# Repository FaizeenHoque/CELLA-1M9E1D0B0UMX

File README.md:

# CELLA 1M9E1D0B0UCX

> A minimal 9-key macropad with rotary encoder. Custom PCB, XIAO RP2040, KMK firmware.

---

## Specs

| | |
|---|---|
| MCU | Seeed XIAO RP2040 |
| Switches | 9× MX-compatible (3×3 matrix) |
| Encoder | 1× rotary with push switch |
| Display | None |
| Bluetooth | No |
| Connector | USB-C |
| Firmware | KMK on CircuitPython |
| PCB | Custom, KiCad |

---

## Naming Convention

`CELLA [V][T][K]E[E#]D[D#]B[B#][CON][CASE]`

| Code | Meaning | Values |
|------|---------|--------|
| `V` | Version | `1`, `2`, `3`... |
| `T` | Type | `M` Macro · `N` Numpad · `D` Dial |
| `K` | Key count | `9`, `12`, `16`... |
| `E#` | Encoder | `E1` yes · `E0` no |
| `D#` | Display | `D1` yes · `D0` no |
| `B#` | Bluetooth | `B1` yes · `B0` no |
| `CON` | Connector | `UC` USB-C · `UM` Micro-B |
| `CASE` | Case | `C` clear · `B` black · `W` white · `X` no case |

**Example:** `CELLA 1M9E1D0B0UCX` — Version 1, Macro, 9 keys, 1 encoder, no display, no bluetooth, USB-C, no case.

---

## Renders

---

## License

© 2025 Faizeen Hoque

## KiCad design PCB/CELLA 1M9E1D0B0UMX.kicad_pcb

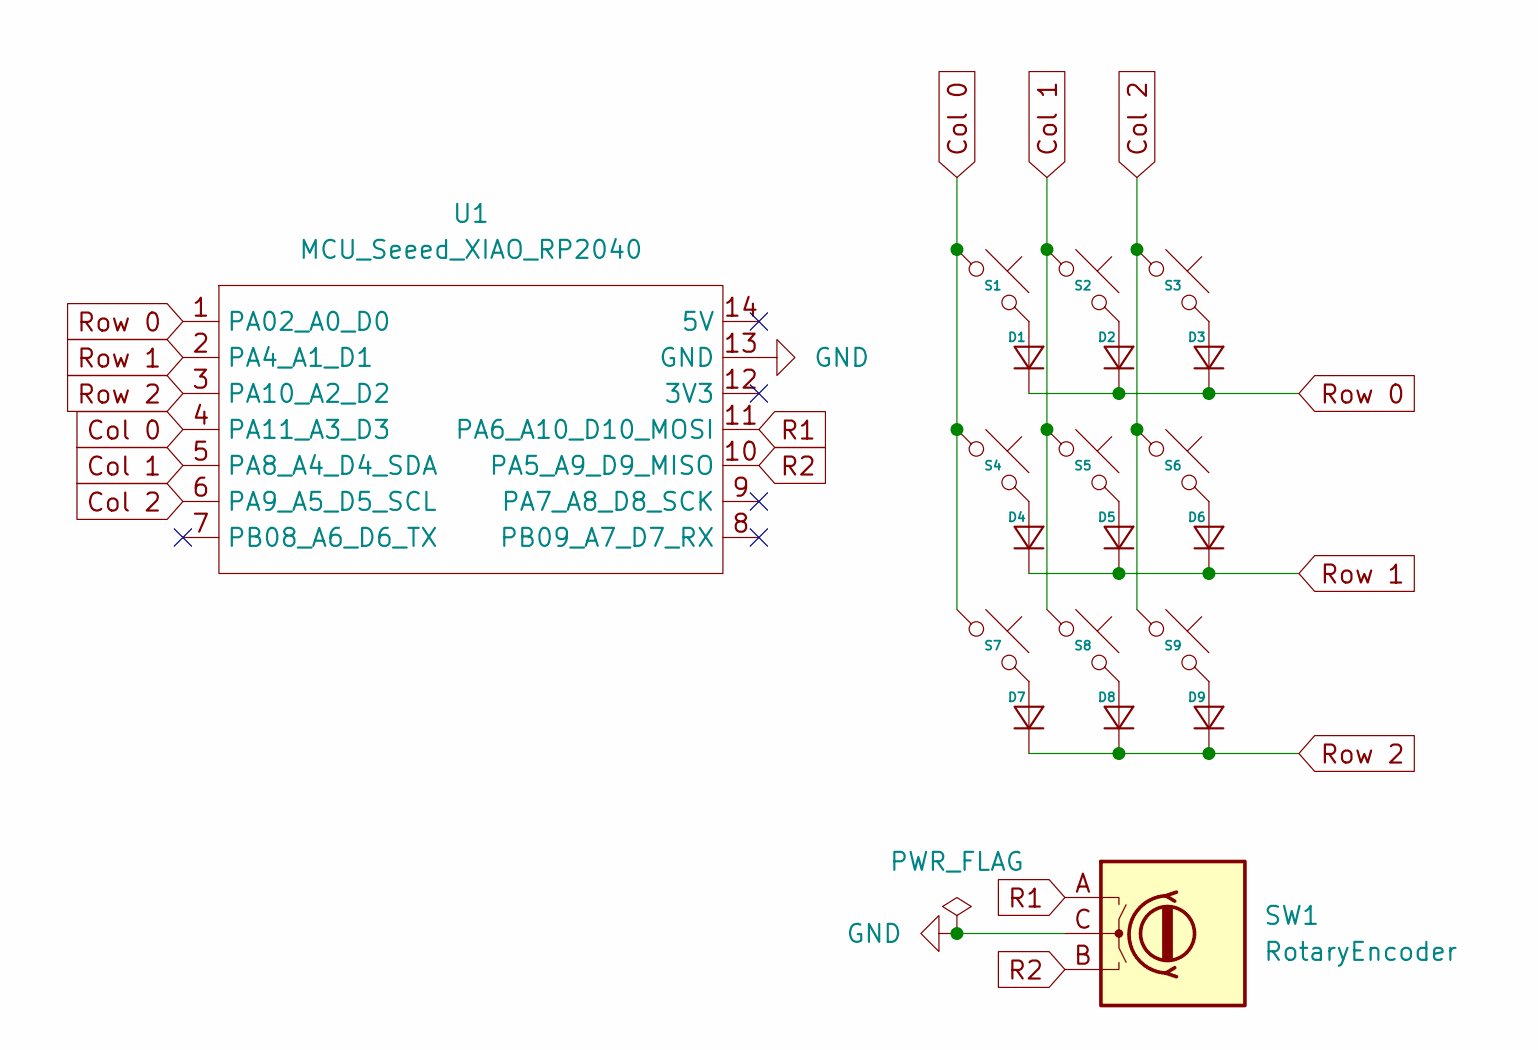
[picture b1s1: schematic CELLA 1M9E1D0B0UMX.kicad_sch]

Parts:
D1, D2, D3, D4, D5, D6, D7, D8, D9: Diode_DO-35
S1, S2, S3, S4, S5, S6, S7, S8, S9: MX_PCB_1.00u
SW1: RotaryEncoder; Encoder_EC11_MX
U1: MCU_Seeed_XIAO_RP2040; Seeed_XIAO_RP2040

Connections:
Col 0: S1.1, S4.1, S7.1, U1.4 (PA11_A3_D3)
Col 1: S2.1, S5.1, S8.1, U1.5 (PA8_A4_D4_SDA)
Col 2: S3.1, S6.1, S9.1, U1.6 (PA9_A5_D5_SCL)
GND: SW1.C, U1.13 (GND)
unnamed: D1.2 (A), S1.2
unnamed: D2.2 (A), S2.2
unnamed: D3.2 (A), S3.2
unnamed: D4.2 (A), S4.2
unnamed: D5.2 (A), S5.2
unnamed: D6.2 (A), S6.2
unnamed: D7.2 (A), S7.2
unnamed: D8.2 (A), S8.2
unnamed: D9.2 (A), S9.2
R1: SW1.A, U1.11 (PA6_A10_D10_MOSI)
R2: SW1.B, U1.10 (PA5_A9_D9_MISO)
Row 0: D1.1 (K), D2.1 (K), D3.1 (K), U1.1 (PA02_A0_D0)
Row 1: D4.1 (K), D5.1 (K), D6.1 (K), U1.2 (PA4_A1_D1)
Row 2: D7.1 (K), D8.1 (K), D9.1 (K), U1.3 (PA10_A2_D2)

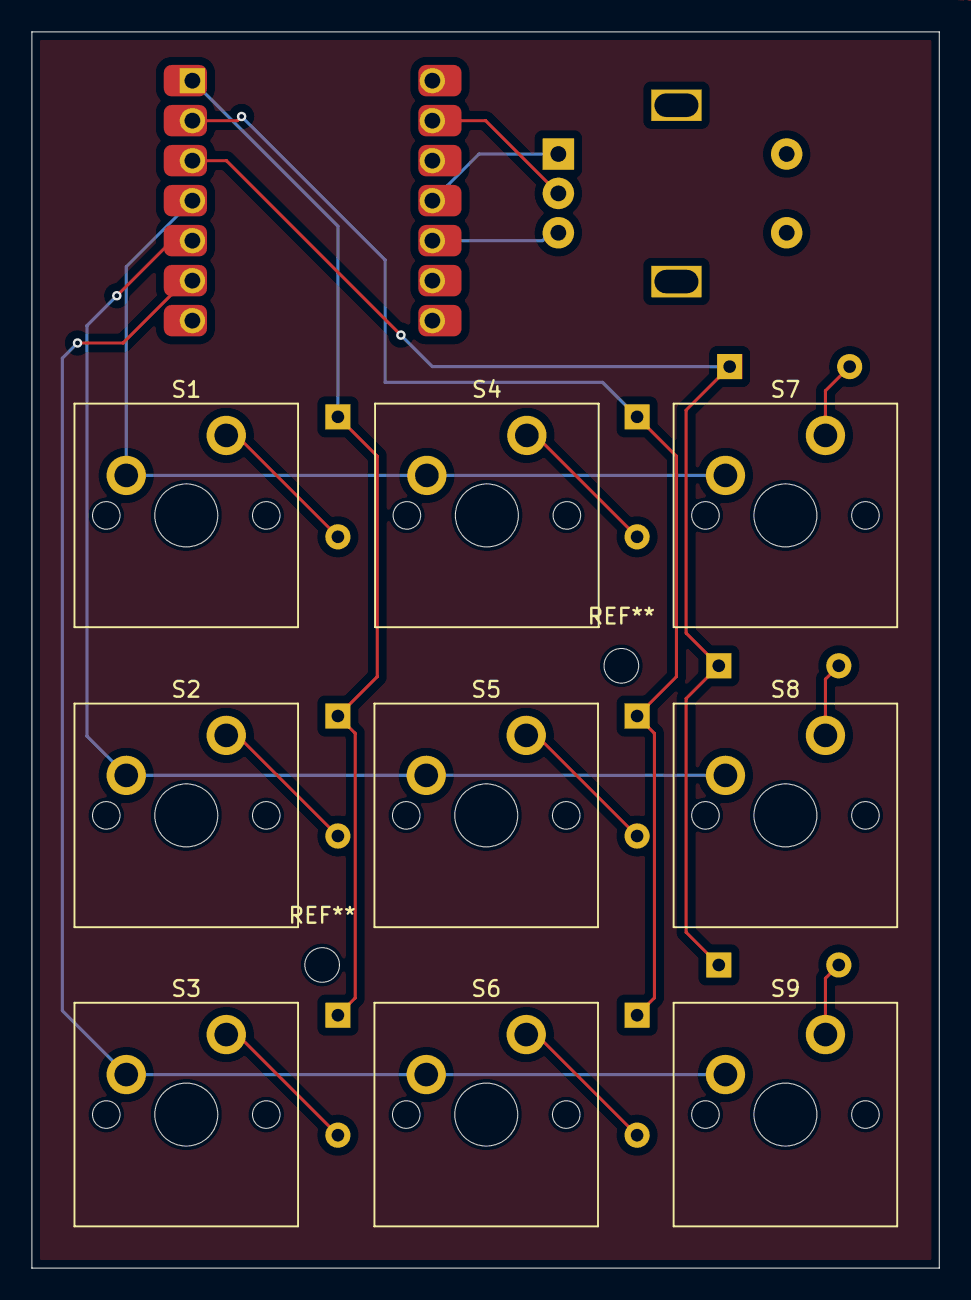
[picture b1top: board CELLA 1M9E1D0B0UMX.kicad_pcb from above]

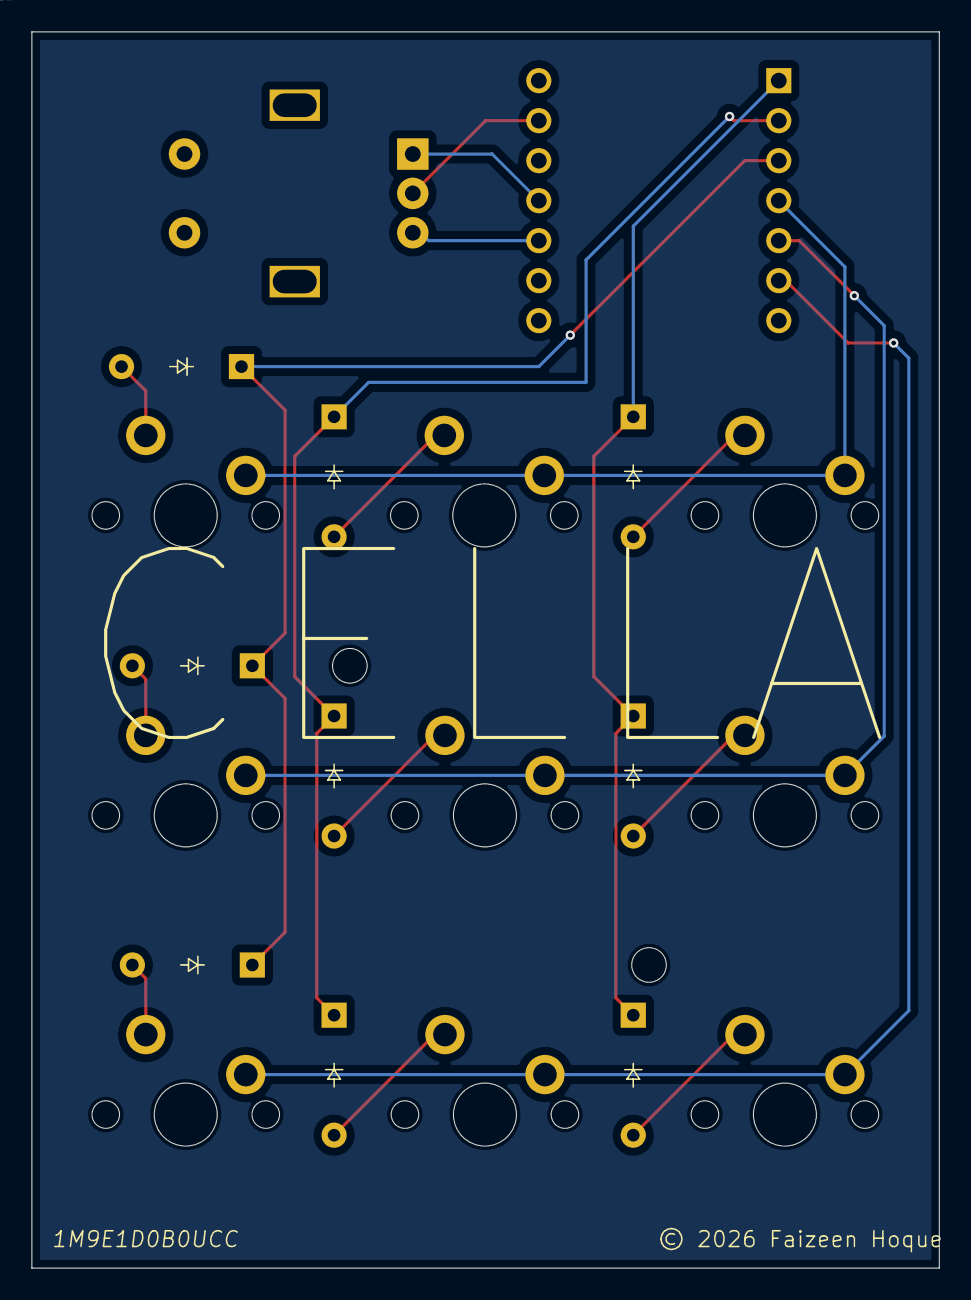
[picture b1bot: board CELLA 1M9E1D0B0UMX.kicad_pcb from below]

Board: 2 copper layers, 57.6 x 78.5 mm, 20 parts (9 on the bottom side), 18 nets.

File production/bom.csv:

Designator,Footprint,Quantity,Value,LCSC Part #
"D1, D2, D3, D4, D5, D6, D7, D8, D9",Diode_DO-35,9,~,
"S1, S2, S3, S4, S5, S6, S7, S8, S9",MX_PCB_1.00u,9,~,
SW1,Encoder_EC11_MX,1,RotaryEncoder,
U1,Seeed_XIAO_RP2040,1,MCU_Seeed_XIAO_RP2040,

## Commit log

2026-03-17 Initial
2026-04-01 Initialize keyboard with keymap and encoder support

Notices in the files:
PCB/CELLA 1M9E1D0B0UMX.kicad_pcb:
© 2026 Faizeen Hoque
